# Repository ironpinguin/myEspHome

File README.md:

# My ESPHome configuration

For the setup please copy config/secrets.yaml.example to config/secrets.yaml and setup the strings with your secrets

Now you can start the docker with `docker-composer up -d` and execute any `esphome` command with `docker-composer exec esphome /bin/bash` or `docker-composer exec esphome esphome logs ...` ....

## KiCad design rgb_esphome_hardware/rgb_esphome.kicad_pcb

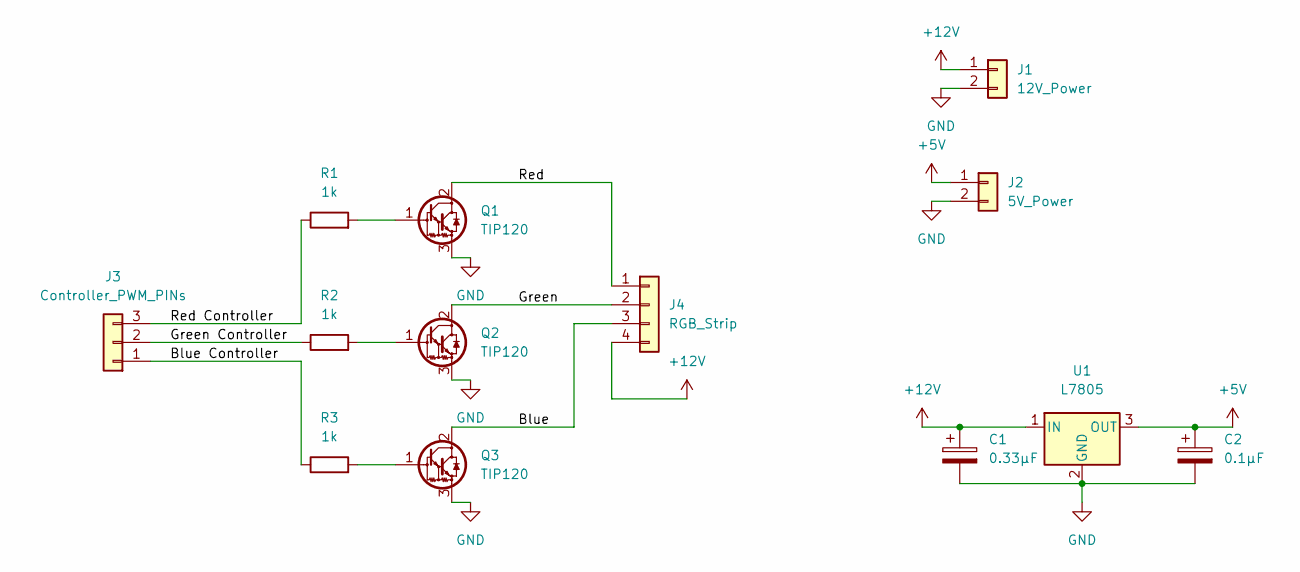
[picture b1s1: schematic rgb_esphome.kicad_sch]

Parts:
C1: 0.33µF; CP_Radial_Tantal_D4.5mm_P5.00mm
C2: 0.1µF; CP_Radial_Tantal_D4.5mm_P5.00mm
J1: 12V_Power; Connector CTB1202_2BK
J2: 5V_Power; PinHeader_1x02_P2.54mm_Horizontal
J3: Controller_PWM_PINs; PinHeader_1x03_P2.54mm_Horizontal
J4: RGB_Strip; Connector CTB1202_4BK
Q1, Q2, Q3: TIP120; TO-220-3_Vertical
R1, R2, R3: 1k; R_Axial_DIN0207_L6.3mm_D2.5mm_P15.24mm_Horizontal
U1: L7805; TO-252-3_TabPin2

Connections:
+5V: C2.1, J2.1, U1.3 (OUT)
+12V: C1.1, J1.1, J4.4, U1.1 (IN)
/Blue: J4.3, Q3.2 (C)
/Blue Controller: J3.1, R3.1
/Green: J4.2, Q2.2 (C)
/Green Controller: J3.2, R2.1
/Red: J4.1, Q1.2 (C)
/Red Controller: J3.3, R1.1
GND: C1.2, C2.2, J1.2, J2.2, Q1.3 (E), Q2.3 (E), Q3.3 (E), U1.2 (GND)
unnamed: Q1.1 (B), R1.2
unnamed: Q2.1 (B), R2.2
unnamed: Q3.1 (B), R3.2

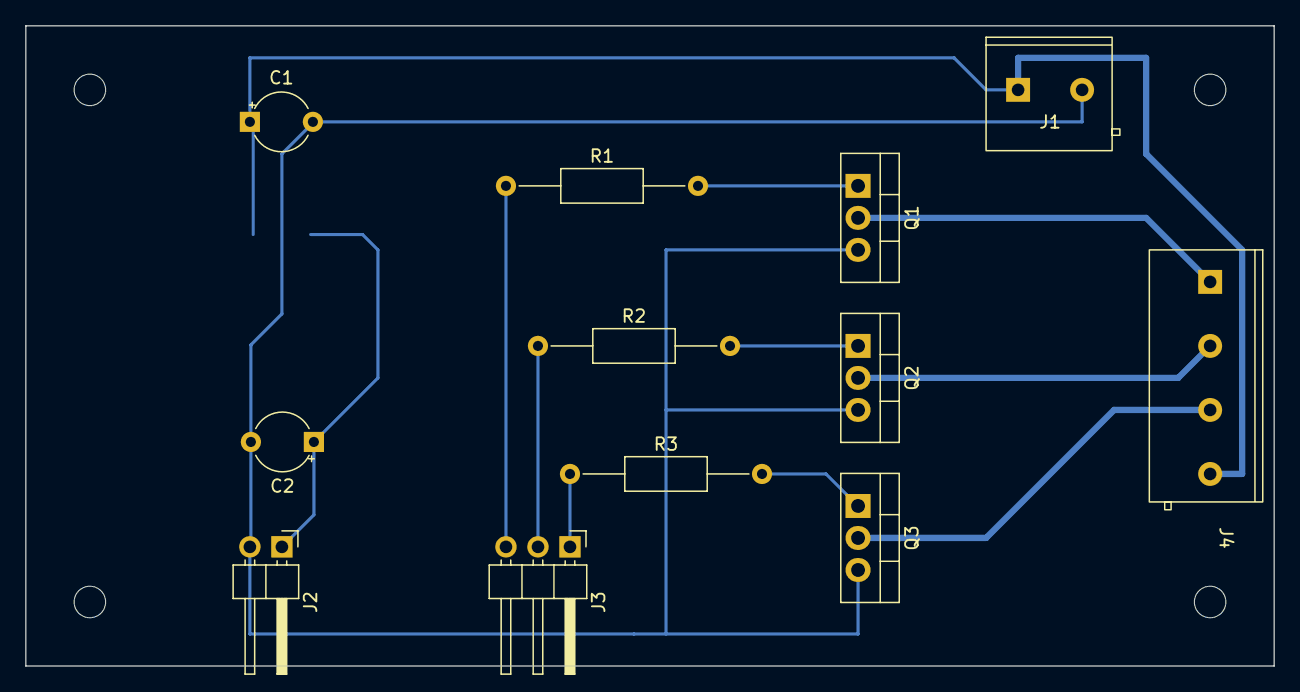
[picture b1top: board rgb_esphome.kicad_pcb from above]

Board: 2 copper layers, 99.1 x 50.8 mm, 13 parts (1 on the bottom side), 12 nets.

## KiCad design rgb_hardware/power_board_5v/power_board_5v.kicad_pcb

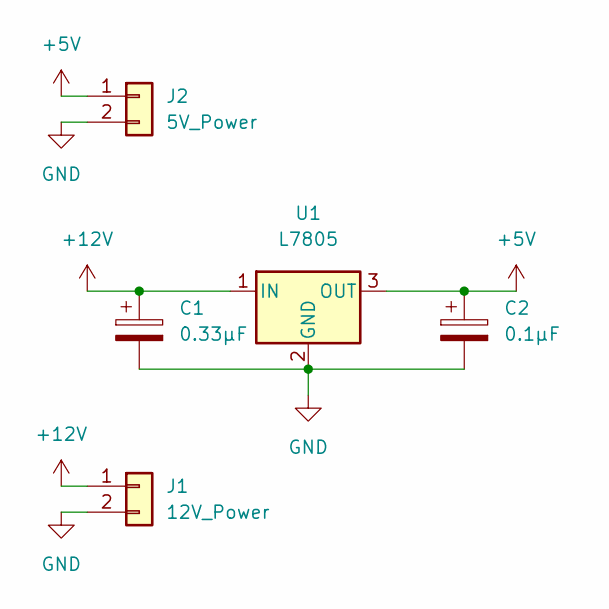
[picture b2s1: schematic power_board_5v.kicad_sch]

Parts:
C1: 0.33µF; CP_Radial_Tantal_D4.5mm_P5.00mm
C2: 0.1µF; CP_Radial_Tantal_D4.5mm_P5.00mm
J1: 12V_Power; Connector CTB1202_2BK
J2: 5V_Power; PinHeader_1x02_P2.54mm_Horizontal
U1: L7805; TO-252-3_TabPin2

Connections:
+5V: C2.1, J2.1, U1.3 (OUT)
+12V: C1.1, J1.1, U1.1 (IN)
GND: C1.2, C2.2, J1.2, J2.2, U1.2 (GND)

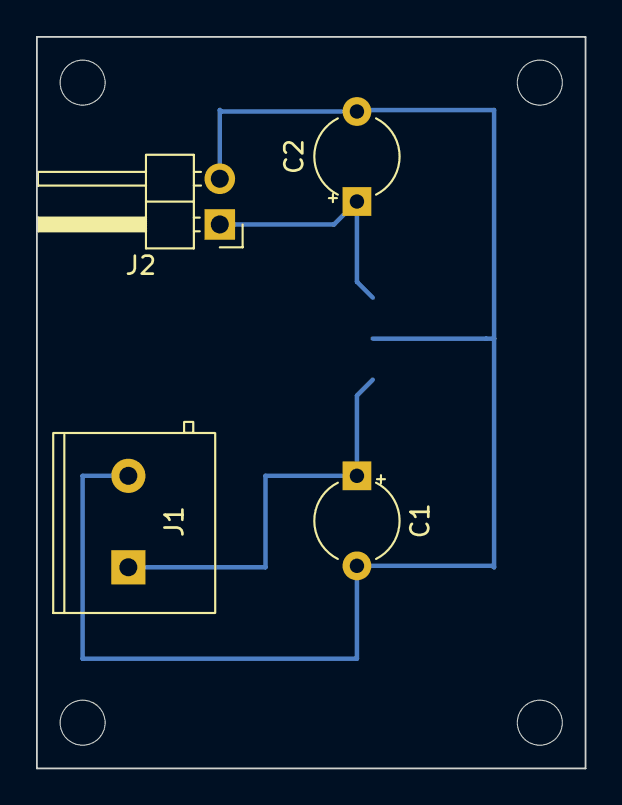
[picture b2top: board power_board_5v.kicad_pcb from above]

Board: 2 copper layers, 30.5 x 40.6 mm, 5 parts (1 on the bottom side), 3 nets.

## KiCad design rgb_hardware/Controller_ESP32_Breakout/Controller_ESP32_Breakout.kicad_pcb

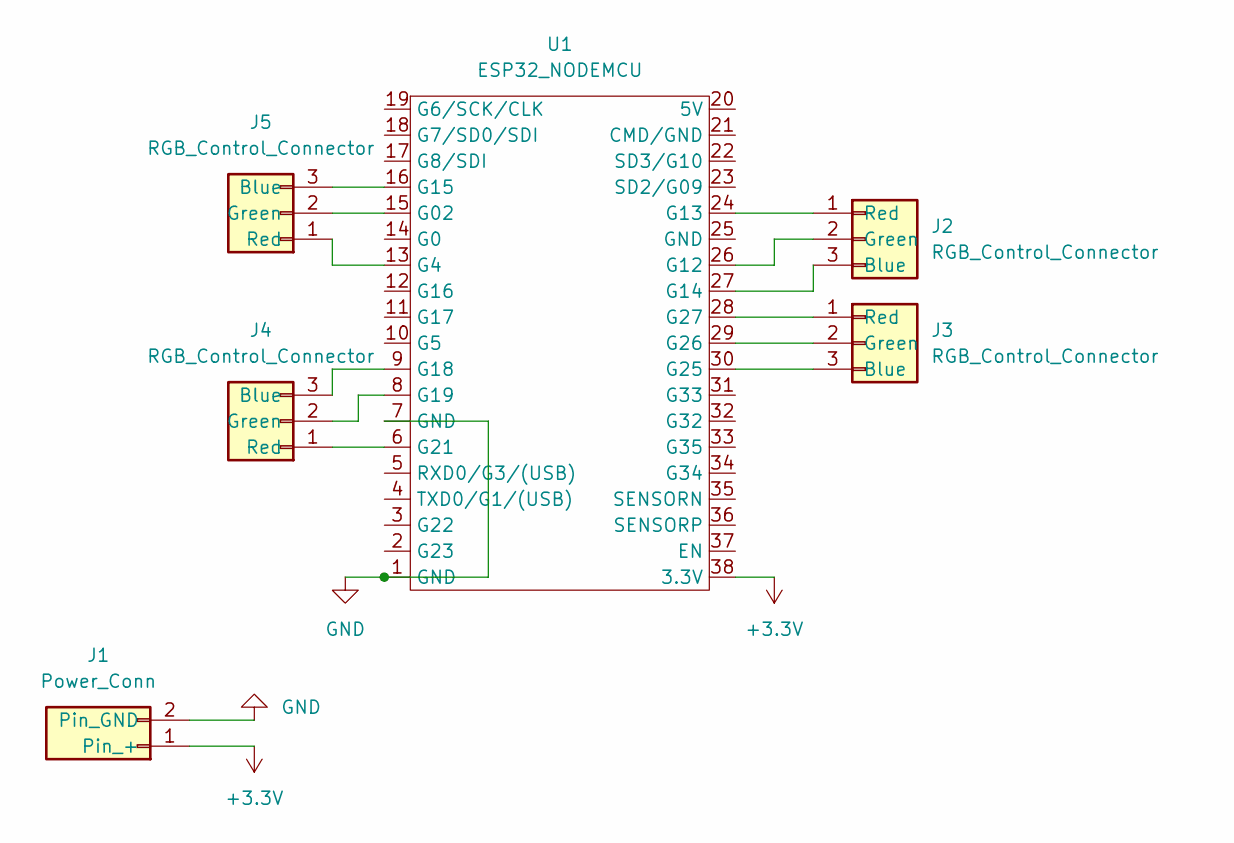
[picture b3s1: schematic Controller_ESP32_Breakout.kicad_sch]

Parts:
J1: Power_Conn; PinHeader_1x02_P2.54mm_Horizontal
J2, J3, J4, J5: RGB_Control_Connector; PinHeader_1x03_P2.54mm_Horizontal
U1: ESP32_NODEMCU; ESP32 NODEMCU

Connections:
+3.3V: J1.1 (Pin_+), U1.38 (3.3V)
GND: J1.2 (Pin_GND), U1.1 (GND), U1.7 (GND)
unnamed: J2.1 (Red), U1.24 (G13)
unnamed: J2.2 (Green), U1.26 (G12)
unnamed: J2.3 (Blue), U1.27 (G14)
unnamed: J3.1 (Red), U1.28 (G27)
unnamed: J3.2 (Green), U1.29 (G26)
unnamed: J3.3 (Blue), U1.30 (G25)
unnamed: J4.1 (Red), U1.6 (G21)
unnamed: J4.2 (Green), U1.8 (G19)
unnamed: J4.3 (Blue), U1.9 (G18)
unnamed: J5.1 (Red), U1.13 (G4)
unnamed: J5.2 (Green), U1.15 (G02)
unnamed: J5.3 (Blue), U1.16 (G15)

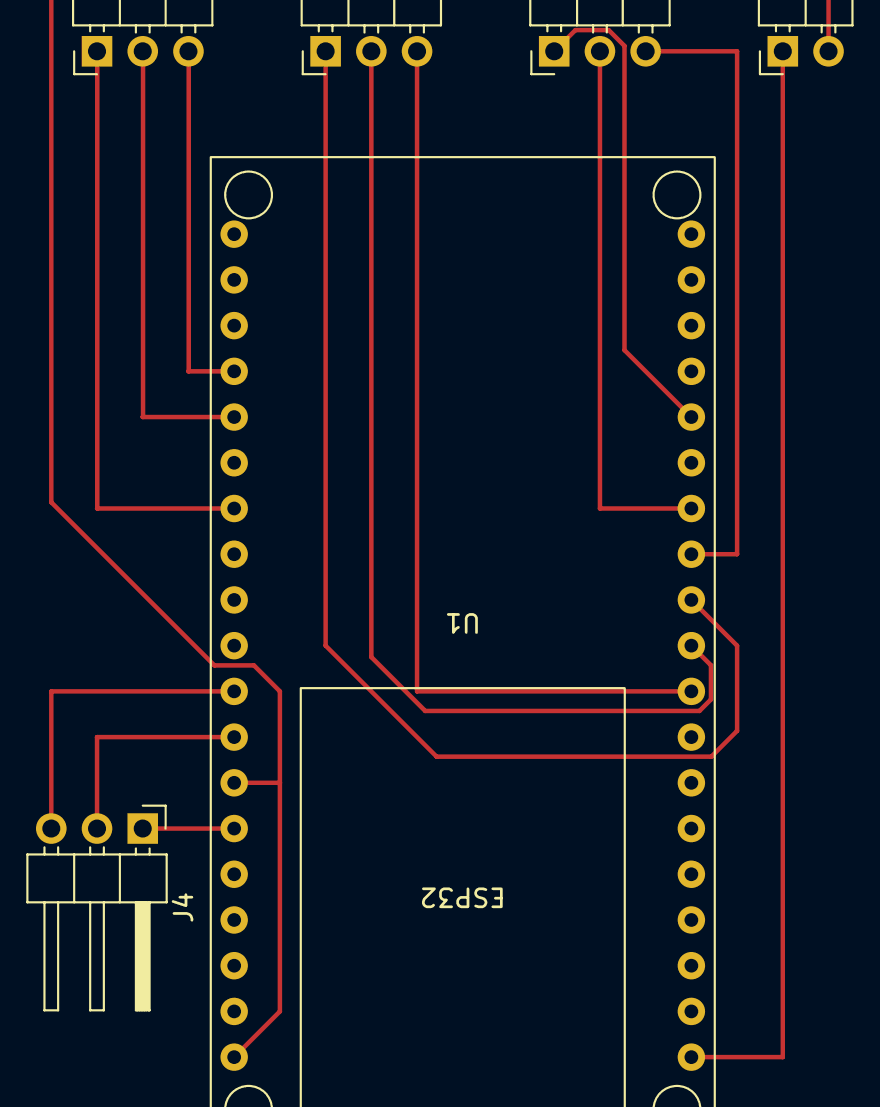
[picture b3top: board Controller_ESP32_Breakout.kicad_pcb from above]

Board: 2 copper layers, 6 parts (0 on the bottom side), 14 nets.

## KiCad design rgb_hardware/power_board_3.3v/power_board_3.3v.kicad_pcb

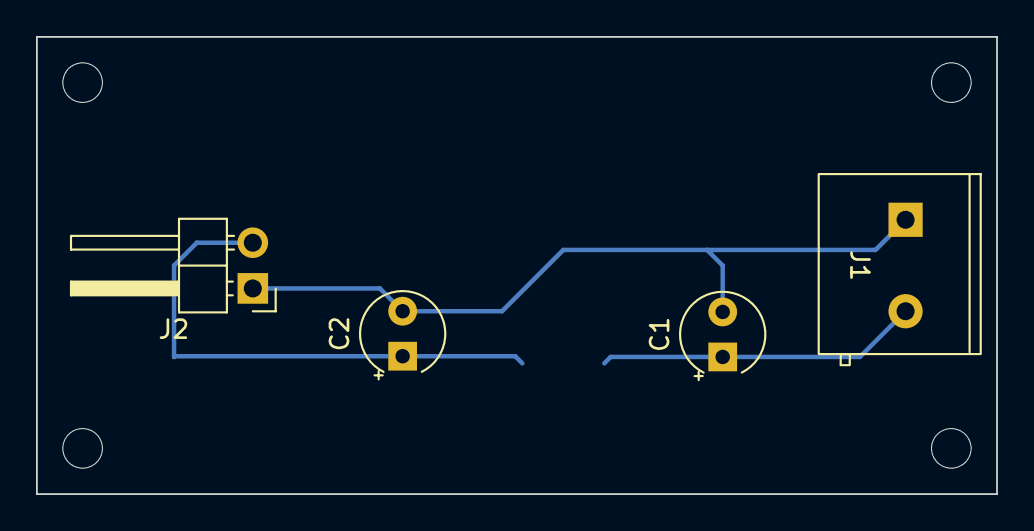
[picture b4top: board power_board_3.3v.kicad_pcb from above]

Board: 2 copper layers, 53.3 x 25.4 mm, 5 parts (1 on the bottom side), 3 nets.

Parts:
C1, C2: 10µF; CP_Radial_Tantal_D4.5mm_P2.50mm
J1: 12V Power; Connector CTB1202_2BK
J2: 3.3V Power; PinHeader_1x02_P2.54mm_Horizontal
U1: TS2937CP33; TO-252-2

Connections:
+3V3: C2.1, J2.2, U1.3 (OUT)
+12V: C1.1, J1.2, U1.1 (IN)
GND: C1.2, C2.2, J1.1, J2.1, U1.2 (GND)

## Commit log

2022-04-01 change from bme680 to bme680_bsec
2022-04-03 change to no strapping pin
2022-08-21 add kicad hardware for rgb strips
2022-08-21 add images
2022-08-22 Split hardware design
2022-09-03 go forward with the esp board
2022-09-03 step forward with the breakout board
2023-08-19 refactor from api password to api crypton preshared key
